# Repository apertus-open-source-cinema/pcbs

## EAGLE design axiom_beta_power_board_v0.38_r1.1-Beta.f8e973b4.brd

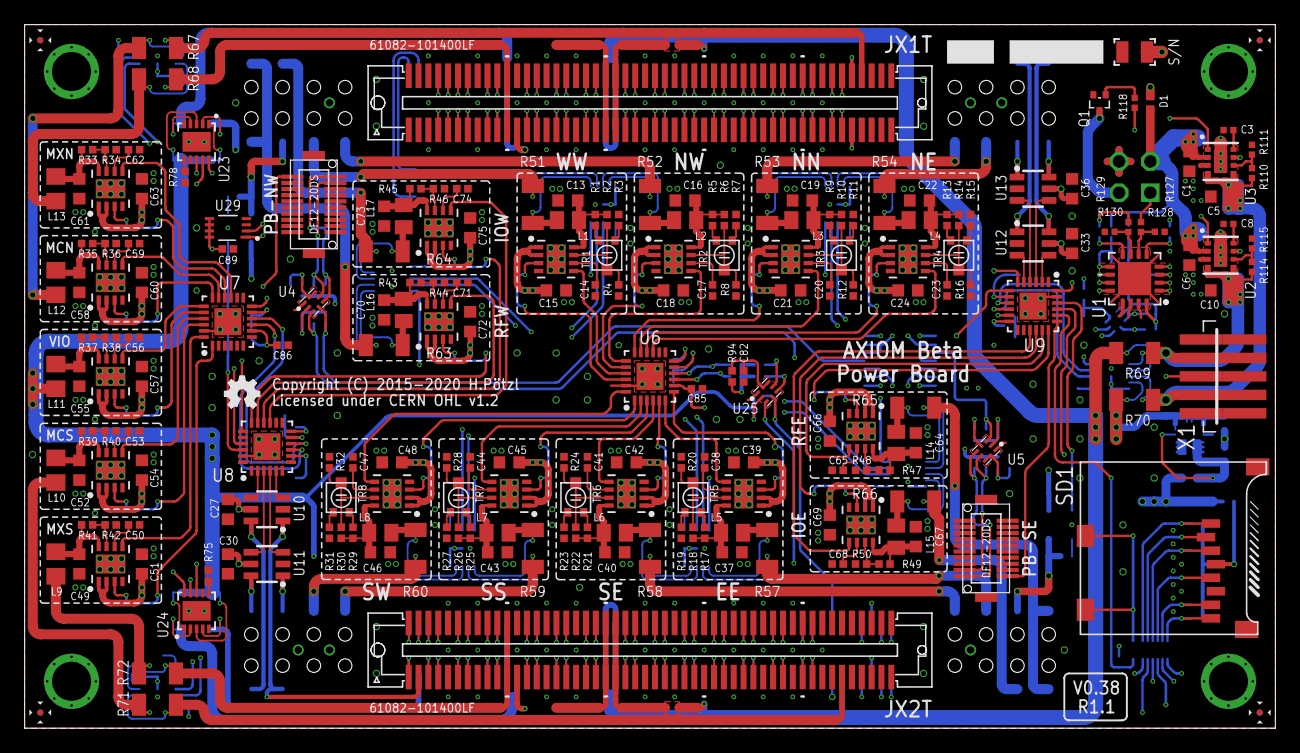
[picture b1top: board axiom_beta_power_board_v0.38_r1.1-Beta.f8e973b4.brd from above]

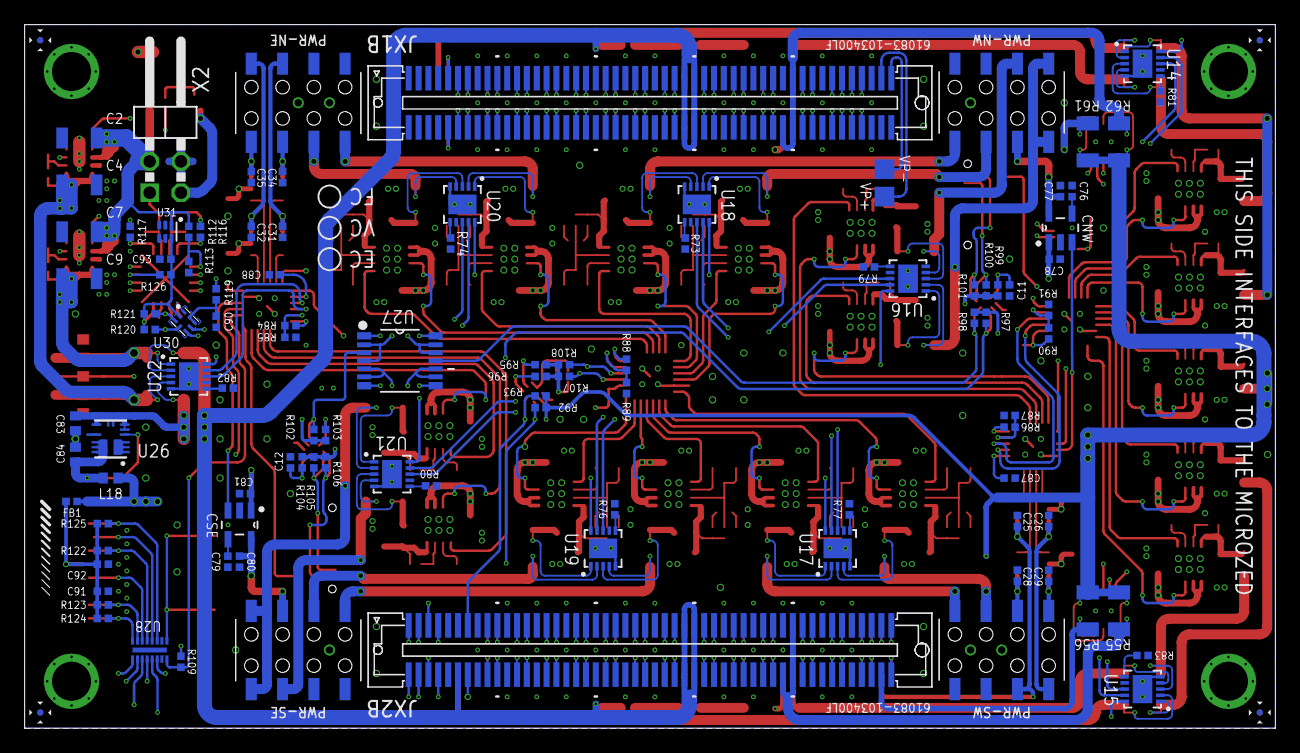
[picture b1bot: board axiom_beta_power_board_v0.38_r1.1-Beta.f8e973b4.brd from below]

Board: 4 copper layers, 101.6 x 57.1 mm, 329 parts (110 on the bottom side), 360 nets.

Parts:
BETA: µZ-FCI-SOCKET-NOHOLES-R; µZ-SOCKET-NOHOLES-R
C1, C5, C6, C10, C15, C18, C21, C24, C39, C42, C45, C48, C51, C54, C57, C60, C63, C66, C69, C72, C75: 10u; 0603-B
C2, C4, C7, C9: 10u; 1206-C
C3, C8: 1n; 0402-C
C11, C12, C76, C79, C82, C90: 10n; 0402-B
C13, C16, C19, C22, C27, C30, C33, C36, C37, C40, C43, C46, C49, C52, C55, C58, C61, C64, C67, C70, C73: 4u7; 0603-B
C14, C17, C20, C23, C38, C41, C44, C47, C50, C53, C56, C59, C62, C65, C68, C71, C74: DNP; 0402-B
C25, C26, C28, C29, C31, C32, C34, C35, C77, C78, C80, C81, C91: 1u; 0402-B
C83, C84: 10u; 0603-C
C85, C86, C87, C88, C89, C92: 100n; 0402-B
C93: 4u7; 0402-B
CNW: SPX3819M5-L-3-3; SOT95P280X145-5N
CSE: SPX3819M5-L-3-3; SOT95P280X145-5N
D1: PMEG2010BELD; DFN1006D-2
EE: MCP1727-ADJE/MF; DFN65P300X300X100-9N
FB1: 0402-B
FID1, FID2, FID3, FID4, FID5, FID6, FID7, FID8: FIDUCIAL; FID_ARROW
IOE: MCP1727-ADJE/MF; DFN65P300X300X100-9N
IOW: MCP1727-ADJE/MF; DFN65P300X300X100-9N
JX1B, JX2B: BERGSTAK-61083F; 61083-FAKE
JX1T, JX2T: BERGSTAK-61082F; 61082-FAKE
L1, L2, L3, L4, L5, L6, L7, L8, L14, L15, L16, L17: 0805-B
L9, L10, L11, L12, L13: 0805-A
L18: 0603-C
LOGO1: OSHW_LOGO_FILLX0100-NT; OSHW_FILLX100_NOTEXT
MCN: MCP1727-ADJE/MF; DFN65P300X300X100-9N
MCS: MCP1727-ADJE/MF; DFN65P300X300X100-9N
MXN: MCP1727-ADJE/MF; DFN65P300X300X100-9N
MXS: MCP1727-ADJE/MF; DFN65P300X300X100-9N
NE: MCP1727-ADJE/MF; DFN65P300X300X100-9N
NN: MCP1727-ADJE/MF; DFN65P300X300X100-9N
NW: MCP1727-ADJE/MF; DFN65P300X300X100-9N
PB-NW: DF12(XX)-20DP-0.5V
PB-SE: DF12(XX)-20DP-0.5V
PWR-NE: PINRC-2X04; R2X04
PWR-NW: PINRC-2X04; R2X04
PWR-SE: PINRC-2X04; R2X04
PWR-SW: PINRC-2X04; R2X04
Q1: NX3008NBKT; SOT416
R1, R5, R9, R13, R17, R21, R25, R29: RA; 0402-B
R2, R6, R10, R14, R18, R22, R26, R30, R33, R35, R39, R41, R43, R45, R47, R49: RB; 0402-B
R3, R7, R11, R15, R19, R23, R27, R31: RC; 0402-B
R4, R8, R12, R16, R20, R24, R28, R32, R34, R36, R40, R42, R44, R46, R48, R50: RD; 0402-B
R37: 102k; 0402-B
R38, R113: 20k; 0402-B
R51, R52, R53, R54, R55, R56, R57, R58, R59, R60, R61, R62, R63, R64, R65, R66, R67, R68, R69, R70, R71, R72: 1206-B
R73: 750R; 0402-B
R74: 1k27; 0402-B
R75: 430R; 0402-B
R76: 0R; 0402-B
R77: 100R; 0402-B
R78: 560R; 0402-B
R79: 5k6; 0402-B
R80: 9k1; 0402-B
R81: 2k0; 0402-B
R82: 1k6; 0402-B
R83: 2k7; 0402-B
R84: 22k; 0402-B
R85, R87, R109, R126: 10k; 0402-B
R86, R88: 13k; 0402-B
R89: 3k; 0402-B
R90: 15k; 0402-B
R91: 1k; 0402-B
R92, R93, R95, R96, R97, R98, R100, R101, R102, R103, R105, R106, R107, R108, R120, R121: 4k7; 0402-B
R94, R99, R104, R119: 200k; 0402-B
R110, R114: 147k; 0402-C
R111, R115: 28k; 0402-C
R112: 180k; 0402-B
R116, R117: 100k; 0402-B
R118: 100k; 0402-C
R122, R123, R124, R125: 50k; 0402-B
R127, R129: 180k; 0402-C
R128, R130: 20k; 0402-C
RFE: MCP1727-ADJE/MF; DFN65P300X300X100-9N
RFW: MCP1727-ADJE/MF; DFN65P300X300X100-9N
S/N: 91658; 3X2MM
SD1: MICRO-SD-2CD; TF-MICRO-SD_PP2
SE: MCP1727-ADJE/MF; DFN65P300X300X100-9N
SS: MCP1727-ADJE/MF; DFN65P300X300X100-9N
SW: MCP1727-ADJE/MF; DFN65P300X300X100-9N
TR1, TR2, TR3, TR4, TR5, TR6, TR7, TR8: PVZ2A; TRIM-PVZ2A
U1: PIC16F15325-JQ; UQFN65P400X400X100-17N
U2, U3: TPS82130SIL-GM; SIL0008D-GM
U4, U5, U25, U30: PCA9306GM; PCA9570GMH
U6, U7, U8, U9: MCP23018-E/MJ; QFN50P400X400X80-25N
U10, U11, U12, U13: AP7312-3333W6-7; SOT23-6
U14, U15, U16, U17, U18, U19, U20, U21, U22, U23, U24: PAC1720; DFN3X3_10LEAD
U26: SC202A; MLPQ-13
U27: TS3A4751; SOP65P640X120-14N
U28: IP4251CZ16-8-TTL; SON40P135X330X55-17N
U29: LM75BGD; SOT996-2/3
U31: NCP715; DFN150X150X50-6N
VIO: MCP1727-ADJE/MF; DFN65P300X300X100-9N
VP+: TPTP16SQ; TP16SQ
VP-: TPTP16SQ; TP16SQ
WW: MCP1727-ADJE/MF; DFN65P300X300X100-9N
X1: PICO-SPOX-5
X2: 2X02/90
ZED: µZ-FCI-CONONLY; µZ-CONONLY

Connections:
!X_MCLR: R126.2, U1.3, U9.24
AB_SCL: R93.2, U25.4, ZED.113
AB_SCL': R96.2, U25.5, U27.9, U27.10, U30.5
AB_SDA: R92.2, U25.3, ZED.114
AB_SDA': R95.2, U25.6, U27.2, U27.4, U30.6
A_!RST: PB-NW.1, U8.19
A_BUS_EN: U9.6, U27.12, U27.13
A_SCL: PB-NW.2, R101.2, U4.5
A_SCL': R98.2, U4.4, U27.11
A_SDA: PB-NW.4, R100.2, U4.6
A_SDA': R97.2, U4.3, U27.1
BANK13_00_N: BETA.89, ZED.89
BANK13_00_P: BETA.87, ZED.87
BANK13_01_N: BETA.90, ZED.90
BANK13_01_P: BETA.88, ZED.88
BANK13_02_N: BETA.93, ZED.93
BANK13_02_P: BETA.91, ZED.91
BANK13_03_N: BETA.94, ZED.94
BANK13_03_P: BETA.92, ZED.92
BANK13_04_N: BETA.195, ZED.195
BANK13_04_P: BETA.193, ZED.193
BANK13_05_N: BETA.196, ZED.196
BANK13_05_P: BETA.194, ZED.194
BANK13_06_N: BETA.199, ZED.199
BANK13_06_P: BETA.197, ZED.197
BANK13_SE_0: BETA.200, ZED.200
BETA_5V: C4.1, C5.1, D1.A, R70.1, R110.1, U3.4, U3.5, U22.3, X1.4, X1.4A
BETA_5V': C15.1, C18.1, C21.1, C24.1, C27.1, C30.1, C33.1, C36.1, C39.1, C42.1, C45.1, C48.1, C51.1, C54.1, C57.1, C60.1, C63.1, C66.1, C69.1, C72.1, C75.1, C78.1, C81.1, C83.1, CNW.1, CSE.1, EE.1, EE.2, IOE.1, IOE.2, IOW.1, IOW.2, MCN.1, MCN.2, MCS.1, MCS.2, MXN.1, MXN.2, MXS.1, MXS.2, NE.1, NE.2, NN.1, NN.2, NW.1, NW.2, R70.2, RFE.1, RFE.2, RFW.1, RFW.2, SE.1, SE.2, SS.1, SS.2, SW.1, SW.2, U10.5, U11.5, U12.5, U13.5, U22.4, U26.5, U26.6, U26.7, U26.8, U26.9, VIO.1, VIO.2, WW.1, WW.2
BETA_5V_EN: R116.2, U1.8, U3.1
BETA_5V_PG: U1.1, U3.7
BTN: R127.1, X2.1
BTN_SENSE: R127.2, R128.1, U1.6
B_!RST: PB-SE.1, U9.19
B_BUS_EN: U9.7, U27.5, U27.6
B_SCL: PB-SE.2, R106.2, U5.5
B_SCL': R103.2, U5.4, U27.8
B_SDA: PB-SE.4, R105.2, U5.6
B_SDA': R102.2, U5.3, U27.3
CD: SD1.CD1, SD1.CD2, U28.1
CD': R109.2, U9.20, U28.16
CLK: SD1.5, U28.6
CMD: R122.2, SD1.3, U28.5
CNW_BYP: C76.1, CNW.4
CNW_EN: CNW.3, U8.22
CSE_BYP: C79.1, CSE.4
CSE_EN: CSE.3, U9.22
CSO_NE_V: BETA.7, R67.2, U14.2
CSO_NW_V: C77.1, CNW.5, PWR-NW.6
CSO_N_V': L12.2, R67.1, U14.1
CSO_SE_V: C80.1, CSE.5, PWR-SE.6
CSO_SW_V: BETA.112, R71.2, U15.2
CSO_S_V': L10.2, R71.1, U15.1
CTRL: X1.3, X1.3A
DAT0: R123.2, SD1.7, U28.7
DAT1: R124.2, SD1.8, U28.8
DAT2: R125.2, SD1.1, U28.3
DAT3: SD1.2, U28.4
EE_EN: EE.3, U6.7
EE_PG: EE.5, U6.6
E_I2C_EN: U9.5, U12.3
E_I2C_V: C31.1, PWR-NE.6, U12.1
E_SPI_EN: U9.2, U12.4
E_SPI_V: C32.1, PWR-NE.8, U12.6
E_VE: PWR-SE.4, R57.2, U19.2
E_VE': L5.2, R57.1, U19.1
FAN: Q1.3, X2.3
FAN_PWM: R118.2, U1.4
GND: BETA.15, BETA.16, BETA.21, BETA.22, BETA.27, BETA.28, BETA.33, BETA.34, BETA.39, BETA.40, BETA.45, BETA.46, BETA.51, BETA.52, BETA.65, BETA.66, BETA.71, BETA.72, BETA.77, BETA.85, BETA.86, BETA.95, BETA.96, BETA.115, BETA.116, BETA.121, BETA.122, BETA.127, BETA.128, BETA.133, BETA.134, BETA.139, BETA.140, BETA.145, BETA.146, BETA.151, BETA.152, BETA.165, BETA.166, BETA.171, BETA.172, BETA.177, BETA.185, BETA.186, BETA.191, BETA.192, C1.2, C2.2, C3.2, C4.2, C5.2, C6.2, C7.2, C8.2, C9.2, C10.2, C11.2, C12.2, C13.2, C14.2, C15.2, C16.2, C17.2, C18.2, C19.2, C20.2, C21.2, C22.2, C23.2, C24.2, C25.2, C26.2, C27.2, C28.2, C29.2, C30.2, C31.2, C32.2, C33.2, C34.2, C35.2, C36.2, C37.2, C38.2, C39.2, C40.2, C41.2, C42.2, C43.2, C44.2, C45.2, C46.2, C47.2, C48.2, C49.2, C50.2, C51.2, C52.2, C53.2, C54.2, C55.2, C56.2, C57.2, C58.2, C59.2, C60.2, C61.2, C62.2, C63.2, C64.2, C65.2, C66.2, C67.2, C68.2, C69.2, C70.2, C71.2, C72.2, C73.2, C74.2, C75.2, C76.2, C77.2, C78.2, C79.2, C80.2, C81.2, C82.2, C83.2, C84.2, C85.2, C86.2, C87.2, C88.2, C89.2, C90.2, C91.2, C92.2, C93.2, CNW.2, CSE.2, EE.4, EE.9, IOE.4, IOE.9, IOW.4, IOW.9, MCN.4, MCN.9, MCS.4, MCS.9, MXN.4, MXN.9, MXS.4, MXS.9, NE.4, NE.9, NN.4, NN.9, NW.4, NW.9, PB-NW.6, PB-SE.6, PWR-NE.2, PWR-NE.4, PWR-NW.1, PWR-NW.3, PWR-SE.1, PWR-SE.3, PWR-SW.2, PWR-SW.4, Q1.2, R3.2, R4.2, R7.2, R8.2, R11.2, R12.2, R15.2, R16.2, R19.2, R20.2, R23.2, R24.2, R27.2, R28.2, R31.2, R32.2, R34.2, R36.2, R38.2, R40.2, R42.2, R44.2, R46.2, R48.2, R50.2, R73.2, R74.2, R75.2, R76.2, R77.2, R78.2, R79.2, R80.2, R81.2, R82.2, R83.2, R85.2, R87.2, R89.2, R91.2, R111.2, R113.2, R115.2, R128.2, R130.2, RFE.4, RFE.9, RFW.4, RFW.9, S/N.1, SD1.6, SD1.MT1, SD1.MT2, SE.4, SE.9, SS.4, SS.9, SW.4, SW.9, U1.13, U1.EP, U2.3, U2.EPAD, U3.3, U3.EPAD, U4.1, U5.1, U6.23, U6.25, U7.23, U7.25, U8.23, U8.25, U9.23, U9.25, U10.2, U11.2, U12.2, U13.2, U14.5, U14.EPAD, U15.5, U15.EPAD, U16.5, U16.EPAD, U17.5, U17.EPAD, U18.5, U18.EPAD, U19.5, U19.EPAD, U20.5, U20.EPAD, U21.5, U21.EPAD, U22.5, U22.EPAD, U23.5, U23.EPAD, U24.5, U24.EPAD, U25.1, U26.10, U27.7, U28.17, U29.4, U30.1, U31.3, VIO.4, VIO.9, WW.4, WW.9, X1.1, X1.1A, X1.5, X1.5A, X2.4, ZED.15, ZED.16, ZED.21, ZED.22, ZED.27, ZED.28, ZED.33, ZED.34, ZED.39, ZED.40, ZED.45, ZED.46, ZED.51, ZED.52, ZED.65, ZED.66, ZED.71, ZED.72, ZED.77, ZED.85, ZED.86, ZED.95, ZED.96, ZED.115, ZED.116, ZED.121, ZED.122, ZED.127, ZED.128, ZED.133, ZED.134, ZED.139, ZED.140, ZED.145, ZED.146, ZED.151, ZED.152, ZED.165, ZED.166, ZED.171, ZED.172, ZED.177, ZED.185, ZED.186, ZED.191, ZED.192
IOE_EN: IOE.3, U9.16
IOE_PG: IOE.5, U9.15
IOE_V: PWR-SE.5, R66.2, R104.1, R105.1, R106.1, U21.4
IOE_V': L15.2, R66.1, U21.3
IOW_EN: IOW.3, U8.16
IOW_PG: IOW.5, U8.15
IOW_V: PWR-NW.5, R64.2, R99.1, R100.1, R101.1, U16.4
IOW_V': L17.2, R64.1, U16.3
JTAG_EN: U8.2, U10.4
JTAG_V: C26.1, PWR-SW.8, U10.6
JX1_00_N: BETA.13, ZED.13
JX1_00_P: BETA.11, ZED.11
JX1_01_N: BETA.14, ZED.14
JX1_01_P: BETA.12, ZED.12
JX1_02_N: BETA.19, ZED.19
JX1_02_P: BETA.17, ZED.17
JX1_03_N: BETA.20, ZED.20
JX1_03_P: BETA.18, ZED.18
JX1_04_N: BETA.25, ZED.25
JX1_04_P: BETA.23, ZED.23
JX1_05_N: BETA.26, ZED.26
JX1_05_P: BETA.24, ZED.24
JX1_06_N: BETA.31, ZED.31
JX1_06_P: BETA.29, ZED.29
JX1_07_N: BETA.32, ZED.32
JX1_07_P: BETA.30, ZED.30
JX1_08_N: BETA.37, ZED.37
JX1_08_P: BETA.35, ZED.35
JX1_09_N: BETA.38, ZED.38
JX1_09_P: BETA.36, ZED.36
JX1_10_N: BETA.43, ZED.43
JX1_10_P: BETA.41, ZED.41
JX1_11_N: BETA.44, ZED.44
JX1_11_P: BETA.42, ZED.42
JX1_12_N: BETA.49, ZED.49
JX1_12_P: BETA.47, ZED.47
JX1_13_N: BETA.50, ZED.50
JX1_13_P: BETA.48, ZED.48
JX1_14_N: BETA.55, ZED.55
JX1_14_P: BETA.53, ZED.53
JX1_15_N: BETA.56, ZED.56
JX1_15_P: BETA.54, ZED.54
JX1_16_N: BETA.63, ZED.63
JX1_16_P: BETA.61, ZED.61
JX1_17_N: BETA.64, ZED.64
JX1_17_P: BETA.62, ZED.62
JX1_18_N: BETA.69, ZED.69
JX1_18_P: BETA.67, ZED.67
JX1_19_N: BETA.70, ZED.70
JX1_19_P: BETA.68, ZED.68
JX1_20_N: BETA.75, ZED.75
JX1_20_P: BETA.73, ZED.73
JX1_21_N: BETA.76, ZED.76
JX1_21_P: BETA.74, ZED.74
JX1_22_N: BETA.83, ZED.83
JX1_22_P: BETA.81, ZED.81
JX1_23_N: BETA.84, ZED.84
JX1_23_P: BETA.82, ZED.82
JX2_00_N: BETA.119, ZED.119
JX2_00_P: BETA.117, ZED.117
JX2_01_N: BETA.120, ZED.120
JX2_01_P: BETA.118, ZED.118
JX2_02_N: BETA.125, ZED.125
JX2_02_P: BETA.123, ZED.123
JX2_03_N: BETA.126, ZED.126
JX2_03_P: BETA.124, ZED.124
JX2_04_N: BETA.131, ZED.131
JX2_04_P: BETA.129, ZED.129
JX2_05_N: BETA.132, ZED.132
JX2_05_P: BETA.130, ZED.130
JX2_06_N: BETA.137, ZED.137
JX2_06_P: BETA.135, ZED.135
JX2_07_N: BETA.138, ZED.138
JX2_07_P: BETA.136, ZED.136
JX2_08_N: BETA.143, ZED.143
JX2_08_P: BETA.141, ZED.141
JX2_09_N: BETA.144, ZED.144
JX2_09_P: BETA.142, ZED.142
JX2_10_N: BETA.149, ZED.149
JX2_10_P: BETA.147, ZED.147
JX2_11_N: BETA.150, ZED.150
JX2_11_P: BETA.148, ZED.148
JX2_12_N: BETA.155, ZED.155
JX2_12_P: BETA.153, ZED.153
JX2_13_N: BETA.156, ZED.156
JX2_13_P: BETA.154, ZED.154
JX2_14_N: BETA.163, ZED.163
JX2_14_P: BETA.161, ZED.161
JX2_15_N: BETA.164, ZED.164
JX2_15_P: BETA.162, ZED.162
JX2_16_N: BETA.169, ZED.169
JX2_16_P: BETA.167, ZED.167
JX2_17_N: BETA.170, ZED.170
JX2_17_P: BETA.168, ZED.168
JX2_18_N: BETA.175, ZED.175
JX2_18_P: BETA.173, ZED.173
JX2_19_N: BETA.176, ZED.176
JX2_19_P: BETA.174, ZED.174
JX2_20_N: BETA.183, ZED.183
JX2_20_P: BETA.181, ZED.181
JX2_21_N: BETA.184, ZED.184
JX2_21_P: BETA.182, ZED.182
JX2_22_N: BETA.189, ZED.189
JX2_22_P: BETA.187, ZED.187
JX2_23_N: BETA.190, ZED.190
JX2_23_P: BETA.188, ZED.188
MCN_EN: MCN.3, U7.18
MCN_PG: MCN.5, U7.17
MCS_EN: MCS.3, U7.22
MCS_PG: MCS.5, U7.21
MXN_EN: MXN.3, U7.16
MXN_PG: MXN.5, U7.15
MXS_EN: MXS.3, U7.1
MXS_PG: MXS.5, U7.24
unnamed: C49.1, L9.1, MXS.8, R41.1
unnamed: C8.1, U2.8
unnamed: C91.1, C92.1, FB1.2, R122.1, R123.1, R124.1, R125.1, SD1.4
unnamed: C90.1, R119.2, U30.7, U30.8
unnamed: C3.1, U3.8
unnamed: R73.1, U18.6
unnamed: Q1.1, R118.1
unnamed: R110.2, R111.1, U3.6
unnamed: R114.2, R115.1, U2.6
unnamed: C11.1, R99.2, U4.7, U4.8
unnamed: C12.1, R104.2, U5.7, U5.8
unnamed: C13.1, L1.1, R1.2, R2.1, WW.8
unnamed: R75.1, U24.6
unnamed: R2.2, R4.1, TR1.2, WW.7
unnamed: R3.1, TR1.1
unnamed: MXS.7, R41.2, R42.1
unnamed: C50.1, MXS.6
unnamed: C64.1, L14.1, R47.1, RFE.8
unnamed: R47.2, R48.1, RFE.7
unnamed: R78.1, U23.6
unnamed: C14.1, WW.6
unnamed: C65.1, RFE.6
unnamed: C67.1, IOE.8, L15.1, R49.1
unnamed: R84.2, R85.1, U9.11
unnamed: R86.2, R87.1, U8.11
unnamed: R1.1, TR1.3
unnamed: C16.1, L2.1, NW.8, R5.2, R6.1
unnamed: NW.7, R6.2, R8.1, TR2.2
unnamed: R7.1, TR2.1
unnamed: C17.1, NW.6
unnamed: IOE.7, R49.2, R50.1
unnamed: C68.1, IOE.6
unnamed: R74.1, U20.6
unnamed: C19.1, L3.1, NN.8, R9.2, R10.1
unnamed: NN.7, R10.2, R12.1, TR3.2
unnamed: R5.1, TR2.3
unnamed: C20.1, NN.6
unnamed: C70.1, L16.1, R43.1, RFW.8
unnamed: R43.2, R44.1, RFW.7
unnamed: R76.1, U19.6
unnamed: C22.1, L4.1, NE.8, R13.2, R14.1
unnamed: NE.7, R14.2, R16.1, TR4.2
unnamed: R11.1, TR3.1
unnamed: C23.1, NE.6
unnamed: C71.1, RFW.6
unnamed: C73.1, IOW.8, L17.1, R45.1
unnamed: R77.1, U17.6
unnamed: C37.1, EE.8, L5.1, R17.2, R18.1
unnamed: EE.7, R18.2, R20.1, TR5.2
unnamed: R9.1, TR3.3
unnamed: C38.1, EE.6
unnamed: IOW.7, R45.2, R46.1
unnamed: C74.1, IOW.6
unnamed: R15.1, TR4.1
unnamed: R79.1, U16.6
unnamed: C40.1, L6.1, R21.2, R22.1, SE.8
unnamed: R22.2, R24.1, SE.7, TR6.2
unnamed: R13.1, TR4.3
unnamed: C41.1, SE.6
unnamed: C82.1, R94.2, U25.7, U25.8
unnamed: R19.1, TR5.1
unnamed: C43.1, L7.1, R25.2, R26.1, SS.8
unnamed: R26.2, R28.1, SS.7, TR7.2
unnamed: R17.1, TR5.3
unnamed: C44.1, SS.6
unnamed: R23.1, TR6.1
unnamed: R80.1, U21.6
unnamed: C46.1, L8.1, R29.2, R30.1, SW.8
unnamed: R30.2, R32.1, SW.7, TR8.2
unnamed: R21.1, TR6.3
unnamed: C47.1, SW.6
unnamed: R27.1, TR7.1
unnamed: R81.1, U14.6
unnamed: R25.1, TR7.3
unnamed: R83.1, U15.6
unnamed: C52.1, L10.1, MCS.8, R39.1
unnamed: MCS.7, R39.2, R40.1
unnamed: C53.1, MCS.6
unnamed: R31.1, TR8.1
unnamed: R82.1, U22.6
unnamed: C55.1, L11.1, R37.1, VIO.8
unnamed: R37.2, R38.1, VIO.7
unnamed: C56.1, VIO.6
unnamed: R29.1, TR8.3
unnamed: C58.1, L12.1, MCN.8, R35.1
unnamed: MCN.7, R35.2, R36.1
unnamed: C59.1, MCN.6
unnamed: C61.1, L13.1, MXN.8, R33.1
unnamed: MXN.7, R33.2, R34.1
unnamed: C62.1, MXN.6
unnamed: R88.2, R89.1, U6.11
unnamed: R90.2, R91.1, U7.11
NE_EN: NE.3, U6.16
NE_PG: NE.5, U6.15
NN_EN: NN.3, U6.18
NN_PG: NN.5, U6.17
NW_EN: NW.3, U6.20
NW_PG: NW.5, U6.19
N_I2C_EN: U9.3, U13.4
N_I2C_V: C35.1, PWR-NE.7, U13.6
N_SPI_EN: U9.4, U13.3
N_SPI_V: C34.1, PWR-NE.5, U13.1
N_VE: PWR-NE.3, R54.2, U20.4
N_VE': L4.2, R54.1, U20.3
N_VN: PWR-NE.1, R53.2, U20.2
N_VN': L3.2, R53.1, U20.1
N_VW: PWR-NW.2, R52.2, U18.4
N_VW': L2.2, R52.1, U18.3
PCIE_N_5V: BETA.59, BETA.60
PCIE_N_V: BETA.79, BETA.80, R68.2, U14.4
PCIE_N_V': L13.2, R68.1, U14.3
PCIE_S_5V: BETA.159, BETA.160
PCIE_S_V: BETA.179, BETA.180, R72.2, U15.4
PCIE_S_V': L9.2, R72.1, U15.3
PCIE_VCCIO: R61.2, U23.2
PEX_N_V: BETA.57, BETA.58
PEX_S_V: BETA.157, BETA.158
PMOD_D0: U28.9, ZED.101
PMOD_D1: U28.10, ZED.102
PMOD_D2: U28.12, ZED.103
PMOD_D3: U28.11, ZED.104
PMOD_D6: U28.14, ZED.107
PMOD_D7: U28.13, ZED.108
PMOD_SCL: R107.2, U6.9, U7.9, U8.9, U9.9, U14.9, U15.9, U16.9, U17.9, U18.9, U19.9, U20.9, U21.9, U22.9, U23.9, U24.9, U29.2, ZED.105
PMOD_SDA: R108.2, U6.10, U7.10, U8.10, U9.10, U14.8, U15.8, U16.8, U17.8, U18.8, U19.8, U20.8, U21.8, U22.8, U23.8, U24.8, U29.1, ZED.106
REGOUT: C84.1, L18.1, U26.4, U26.11, U26.12, U26.13
RFE_EN: RFE.3, U9.18
RFE_PG: RFE.5, U9.17
RFE_V: PWR-SE.7, R65.2, U21.2
RFE_V': L14.2, R65.1, U21.1
RFW_EN: RFW.3, U8.18
RFW_PG: RFW.5, U8.17
RFW_V: PWR-NW.7, R63.2, U16.2
RFW_V': L16.2, R63.1, U16.1
SE_0: BETA.9, ZED.9
SE_1: BETA.10, ZED.10
SE_EN: SE.3, U6.5
SE_PG: SE.5, U6.4
SN_SENSE: S/N.2, U1.10
SS_EN: SS.3, U6.3
SS_PG: SS.5, U6.2
SW_EN: SW.3, U6.1
SW_PG: SW.5, U6.24
S_I2C_EN: U8.3, U11.4
S_I2C_V: C29.1, PWR-SW.7, U11.6
S_SPI_EN: U8.4, U11.3
S_SPI_V: C28.1, PWR-SW.5, U11.1
S_VE: PWR-SE.2, R58.2, U19.4
S_VE': L6.2, R58.1, U19.3
S_VS: PWR-SW.1, R59.2, U17.2
S_VS': L7.2, R59.1, U17.1
S_VW: PWR-SW.3, R60.2, U17.4
S_VW': L8.2, R60.1, U17.3
VCC: C85.1, C86.1, C87.1, C88.1, C89.1, FB1.1, L18.2, R84.1, R86.1, R88.1, R90.1, R94.1, R95.1, R96.1, R97.1, R98.1, R102.1, R103.1, R107.1, R108.1, R109.1, R116.1, R117.1, R119.1, R129.1, U4.2, U5.2, U6.8, U6.12, U7.8, U7.12, U8.8, U8.12, U9.8, U9.12, U14.10, U15.10, U16.10, U17.10, U18.10, U19.10, U20.10, U21.10, U22.10, U23.10, U24.10, U27.14, U29.5, U29.6, U29.7, U29.8
VCCIO: L11.2, R55.1, R56.1, R61.1, R62.1, R92.1, R93.1, U23.1, U23.3, U24.1, U24.3, U25.2
VCCO_13: R56.2, U24.4, ZED.198
VCCO_34: R62.2, U23.4, ZED.78, ZED.79, ZED.80
VCCO_35: R55.2, U24.2, ZED.178, ZED.179, ZED.180
VCC_SENSE: R129.2, R130.1, U1.7
VIN: C1.1, C2.1, C6.1, C7.1, D1.C, R112.1, U2.2, U3.2, U31.1, X2.2
VIN_SENSE: R112.2, R113.1, U1.9
VIO_EN: U7.20, VIO.3
VIO_PG: U7.19, VIO.5
VP_0_N: VP-.TP, ZED.99
VP_0_P: VP+.TP, ZED.97
VSB: C93.1, R120.1, R121.1, R126.1, U1.16, U30.2, U31.6
WW_EN: U6.22, WW.3
WW_PG: U6.21, WW.5
W_I2C_EN: U8.5, U10.3
W_I2C_V: C25.1, PWR-SW.6, U10.1
W_VW: PWR-NW.4, R51.2, U18.2
W_VW': L1.2, R51.1, U18.1
X_SCL: R120.2, U1.11, U30.4
X_SDA: R121.2, U1.12, U30.3
ZED_5V: C9.1, C10.1, R69.1, R114.1, U2.4, U2.5, U22.1, X1.2, X1.2A
ZED_5V': R69.2, U22.2, ZED.57, ZED.58, ZED.59, ZED.60, ZED.112, ZED.157, ZED.158, ZED.159, ZED.160
ZED_5V_EN: R117.2, U1.5, U2.1
ZED_5V_PG: U1.2, U2.7

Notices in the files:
axiom_beta_power_board_v0.38_r1.1-Beta.f8e973b4.brd:
Copyright (C) 2015-2020 H.Pötzl
Licensed under CERN OHL v1.2
